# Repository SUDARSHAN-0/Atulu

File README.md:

# Atulu
A smart aesthetic Environment monitoring system for your desk

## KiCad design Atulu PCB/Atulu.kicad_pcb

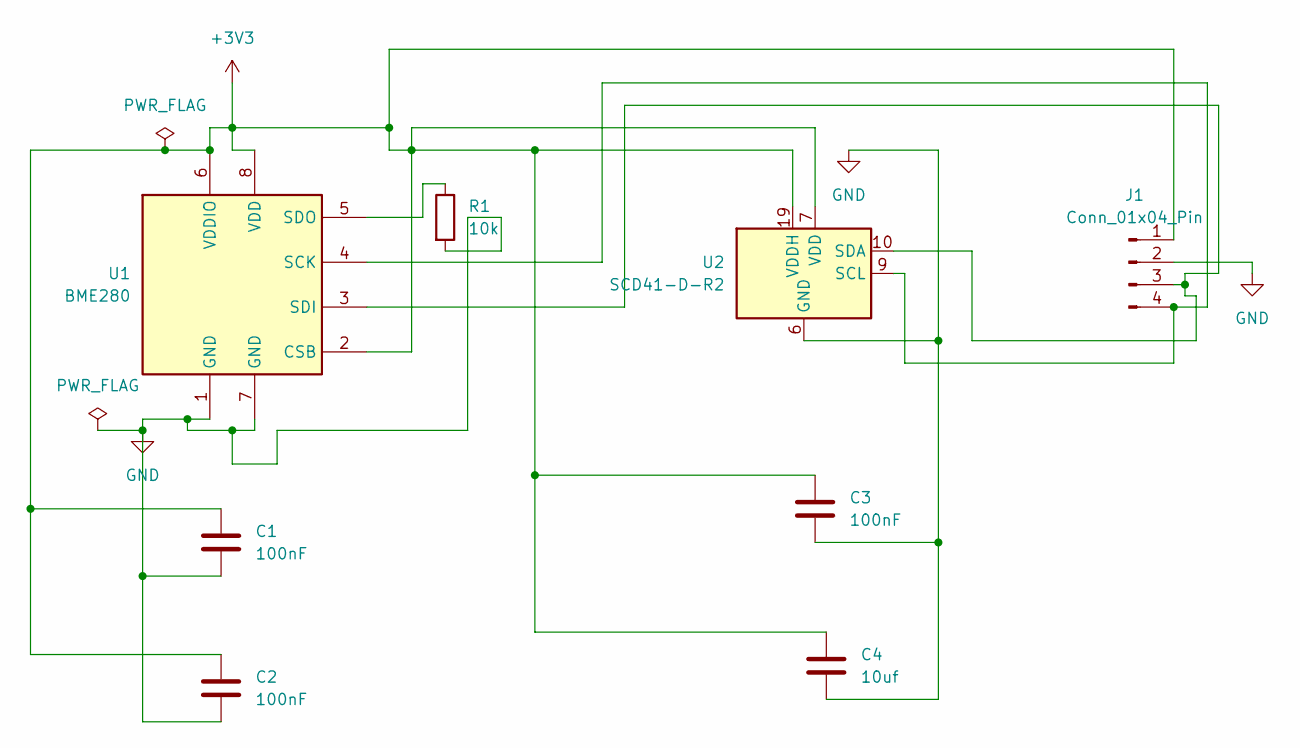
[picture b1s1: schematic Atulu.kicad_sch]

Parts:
C1, C2, C3: 100nF; C_0603_1608Metric
C4: 10uf; C_0603_1608Metric
J1: Conn_01x04_Pin; FanPinHeader_1x04_P2.54mm_Vertical
R1: 10k; R_0603_1608Metric
U1: BME280; Bosch_LGA-8_2.5x2.5mm_P0.65mm_ClockwisePinNumbering
U2: SCD41-D-R2; Sensirion_SCD4x-1EP_10.1x10.1mm_P1.25mm_EP4.8x4.8mm

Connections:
+3V3: C1.1, C2.1, C3.1, C4.1, J1.1, U1.2 (CSB), U1.6 (VDDIO), U1.8 (VDD), U2.7 (VDD), U2.19 (VDDH)
GND: C1.2, C2.2, C3.2, C4.2, J1.2, R1.2, U1.1 (GND), U1.7 (GND), U2.6 (GND), U2.20 (GND), U2.21 (GND)
unnamed: J1.3, U1.3 (SDI), U2.10 (SDA)
unnamed: J1.4, U1.4 (SCK), U2.9 (SCL)
unnamed: R1.1, U1.5 (SDO)

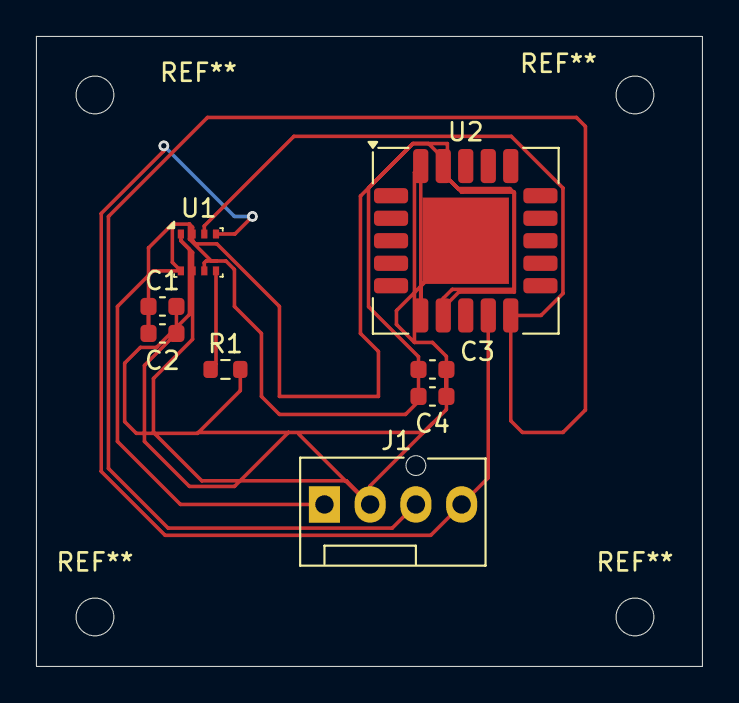
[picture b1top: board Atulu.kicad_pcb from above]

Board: 2 copper layers, 37.0 x 35.0 mm, 8 parts (0 on the bottom side), 5 nets.
